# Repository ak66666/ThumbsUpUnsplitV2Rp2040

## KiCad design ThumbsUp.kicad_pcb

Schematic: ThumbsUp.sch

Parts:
BOOTSEL1: TL1016AAF220QG; Manufacturer_Part_Number TL1016AAF220QG; Mouser Part Number 612-TL1016AAF220QG
C1, C2, C6, C7, C10, C13, C14, C15, C16, C17: 0.1uF; C_0805_2012Metric
C3, C12: 1uF; C_0805_2012Metric
C4, C5: 27pF; C_0805_2012Metric
C9, C11: 10uF; C_0805_2012Metric
D1, D2, D3, D4, D5, D6, D7, D8, D9, D10, D11, D12, D13, D14, D15, D16, D17, D18, D19, D20, D21, D22, D23, D24, D25, D26, D27, D28, D29, D30, D31, D32, D33, D34, D35, D36, D37, D38, D39, D40, D41, D42, D43, D44: D_Small; D_SOD-123
F1: Polyfuse; Fuse_1206_3216Metric
H1, H2, H3: MountingHole_Pad; MountingHole_6.4mm_M6_Pad_Via
IC1: RP2040; QFN40P700X700X90-57N-D; Manufacturer_Part_Number RP2040
IC2: W25Q128JVSIM; SOIC127P790X216-8N; Manufacturer_Part_Number W25Q128JVSIM; Mouser Part Number 454-W25Q128JVSIM
J1, J2, J4, J6, J7, J8, J24, J25, J26, J27: Conn_01x04_Male; PinHeader_1x04_P2.54mm_Vertical
J3, J5, J20, J21, J22, J23, J28, J29, J30, J31: Conn_01x04_Female; PinSocket_1x04_P2.54mm_Vertical
J9, J11, J13, J15, J17: Raiser_Female; PinSocket_1x04_P2.54mm_Vertical
J10, J12, J14, J16, J18: Raiser_Male; PinHeader_1x04_P2.54mm_Vertical
J19: 52559-1233; 525591233; Mouser Part Number 538-52559-1233
J32: USB_C_Receptacle_USB2.0; USB_C_Receptacle_Palconn_UTC16-G
J33: STX-3501-3N; STX35013N; Manufacturer_Part_Number STX-3501-3N; Mouser Part Number 806-STX-3501-3N
MX1: SwESC; Kailh_socket_PG1350_optional
MX2: SwTAB; Kailh_socket_PG1350_optional
MX3: SwLCTL; Kailh_socket_PG1350_optional
MX4: SwQ; Kailh_socket_PG1350_optional
MX5: SwA; Kailh_socket_PG1350_optional
MX6: SwZ; Kailh_socket_PG1350_optional
MX7: SwW; Kailh_socket_PG1350_optional
MX8: SwS; Kailh_socket_PG1350_optional
MX9: SwX; Kailh_socket_PG1350_optional
MX10: SwLWIN; Kailh_socket_PG1350_optional
MX11: SwE; Kailh_socket_PG1350_optional
MX12: SwD; Kailh_socket_PG1350_optional
MX13: SwC; Kailh_socket_PG1350_optional
MX14: SwLALT; Kailh_socket_PG1350_optional
MX15: SwR; Kailh_socket_PG1350_optional
MX16: SwF; Kailh_socket_PG1350_optional
MX17: SwV; Kailh_socket_PG1350_optional
MX18: SwLMOD; Kailh_socket_PG1350_optional
MX19: SwT; Kailh_socket_PG1350_optional
MX20: SwG; Kailh_socket_PG1350_optional
MX21: SwB; Kailh_socket_PG1350_optional
MX22: SwLSHFT; Kailh_socket_PG1350_optional
MX23: SwY; Kailh_socket_PG1350_optional
MX24: SwH; Kailh_socket_PG1350_optional
MX25: SwN; Kailh_socket_PG1350_optional
MX26: SwRSHFT; Kailh_socket_PG1350_optional
MX27: SwU; Kailh_socket_PG1350_optional
MX28: SwJ; Kailh_socket_PG1350_optional
MX29: SwM; Kailh_socket_PG1350_optional
MX30: SwRMOD; Kailh_socket_PG1350_optional
MX31: SwI; Kailh_socket_PG1350_optional
MX32: SwK; Kailh_socket_PG1350_optional
MX33: SwCOMMA; Kailh_socket_PG1350_optional
MX34: SwRALT; Kailh_socket_PG1350_optional
MX35: SwO; Kailh_socket_PG1350_optional
MX36: SwL; Kailh_socket_PG1350_optional
MX37: SwDOT; Kailh_socket_PG1350_optional
MX38: SwMENU; Kailh_socket_PG1350_optional
MX39: SwP; Kailh_socket_PG1350_optional
MX40: SwCOLON; Kailh_socket_PG1350_optional
MX41: Sw?; Kailh_socket_PG1350_optional
MX42: SwBKSP; Kailh_socket_PG1350_optional
MX43: SwENTER; Kailh_socket_PG1350_optional
MX44: SwRCTRL; Kailh_socket_PG1350_optional
R1, R2: 27.4; R_0805_2012Metric
R3: 10k; R_0805_2012Metric
R4, R5: 4.7k; R_0805_2012Metric
R6: 1k; R_0805_2012Metric
R7: DNF; R_0805_2012Metric
R8, R9: 5.1k; R_0805_2012Metric
RUN1: TL1016AAF220QG; Manufacturer_Part_Number TL1016AAF220QG; Mouser Part Number 612-TL1016AAF220QG
U1: NCP1117-3.3_SOT223; SOT-223-3_TabPin2
Y1: ABLS-12.000MHZ-B4-T; HC%2f49US-(AT49)_1

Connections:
+1V1: C12.1, C13.1, C14.1, IC1.23 (DVDD_1), IC1.45 (VREG_VOUT), IC1.50 (DVDD_2)
+3V3: C1.1, C2.1, C3.1, C6.1, C7.1, C10.1, C11.1, C15.1, C16.1, C17.1, IC1.1 (IOVDD_1), IC1.10 (IOVDD_2), IC1.22 (IOVDD_3), IC1.33 (IOVDD_4), IC1.42 (IOVDD_5), IC1.43 (ADC_AVDD), IC1.44 (VREG_VIN), IC1.48 (USB_VDD), IC1.49 (IOVDD_6), IC2.8 (VCC), J18.1, R4.1, R5.2, R7.2, U1.2 (VO)
+5V: C9.1, F1.1, U1.3 (VI)
COL0: IC1.35 (GPIO23), J20.4
COL1: IC1.36 (GPIO24), J20.3
COL2: IC1.37 (GPIO25), J20.2, MX10.1 (COL)
COL3: IC1.38 (GPIO26/ADC0), J20.1, MX14.1 (COL)
COL4: IC1.34 (GPIO22), J4.1, MX15.1 (COL), MX16.1 (COL), MX17.1 (COL)
COL5: IC1.39 (GPIO27/ADC1), J4.4, MX19.1 (COL), MX20.1 (COL), MX21.1 (COL)
COL6: IC1.5 (GPIO3), J6.1, MX23.1 (COL), MX24.1 (COL), MX25.1 (COL)
COL7: IC1.4 (GPIO2), J6.4, MX27.1 (COL), MX28.1 (COL), MX29.1 (COL)
COL8: IC1.6 (GPIO4), J24.1, MX34.1 (COL)
COL9: IC1.7 (GPIO5), J24.2, MX38.1 (COL)
COLA: IC1.8 (GPIO6), J24.3
COLB: IC1.9 (GPIO7), J24.4
D+: J32.A6 (D+), J32.B6 (D+), R2.2
D-: J32.A7 (D-), J32.B7 (D-), R1.2
GND: BOOTSEL1.3, BOOTSEL1.4, C1.2, C2.2, C3.2, C4.2, C5.2, C6.2, C7.2, C9.2, C10.2, C11.2, C12.2, C13.2, C14.2, C15.2, C16.2, C17.2, IC1.19 (TESTEN), IC1.57 (GND), IC2.4 (GND), J11.1, J11.2, J11.3, J11.4, J15.1, J15.2, J15.3, J15.4, J18.4, J32.A1 (GND), J32.A12 (GND), J32.B1 (GND), J32.B12 (GND), J32.S1 (SHIELD), R8.2, R9.1, RUN1.3, RUN1.4, U1.1 (GND)
GND-TOP: J17.4, J19.11
unnamed: BOOTSEL1.1, BOOTSEL1.2, R3.1
unnamed: C5.1, R6.2, Y1.1
unnamed: D1.2 (A), J21.4
unnamed: D2.2 (A), J21.3
unnamed: D3.2 (A), J21.2
unnamed: D4.2 (A), J21.1
unnamed: D5.2 (A), J22.4
unnamed: D6.2 (A), J22.3
unnamed: D7.2 (A), J22.2
unnamed: D8.2 (A), J22.1
unnamed: D9.2 (A), J23.4
unnamed: D10.2 (A), J23.3
unnamed: D11.2 (A), J23.2
unnamed: D12.2 (A), J23.1
unnamed: D13.2 (A), MX14.2 (ROW)
unnamed: D14.2 (A), MX10.2 (ROW)
unnamed: D15.2 (A), MX15.2 (ROW)
unnamed: D16.2 (A), MX16.2 (ROW)
unnamed: D17.2 (A), MX17.2 (ROW)
unnamed: D18.2 (A), J4.2
unnamed: D19.2 (A), J4.3
unnamed: D20.2 (A), MX19.2 (ROW)
unnamed: D21.2 (A), MX20.2 (ROW)
unnamed: D22.2 (A), MX21.2 (ROW)
unnamed: D23.2 (A), MX23.2 (ROW)
unnamed: D24.2 (A), MX24.2 (ROW)
unnamed: D25.2 (A), MX25.2 (ROW)
unnamed: D26.2 (A), MX27.2 (ROW)
unnamed: D27.2 (A), MX28.2 (ROW)
unnamed: D28.2 (A), MX29.2 (ROW)
unnamed: D29.2 (A), J6.2
unnamed: D30.2 (A), J6.3
unnamed: D31.2 (A), J25.4
unnamed: D32.2 (A), J25.3
unnamed: D33.2 (A), J25.2
unnamed: D34.2 (A), J25.1
unnamed: D35.2 (A), J26.4
unnamed: D36.2 (A), J26.3
unnamed: D37.2 (A), J26.2
unnamed: D38.2 (A), J26.1
unnamed: D39.2 (A), J27.4
unnamed: D40.2 (A), J27.3
unnamed: D41.2 (A), J27.2
unnamed: D42.2 (A), J27.1
unnamed: D43.2 (A), MX34.2 (ROW)
unnamed: D44.2 (A), MX38.2 (ROW)
unnamed: F1.2, J32.A4 (VBUS), J32.A9 (VBUS), J32.B4 (VBUS), J32.B9 (VBUS)
unnamed: H1.1, H2.1, H3.1, J12.1, J12.2, J12.3, J12.4, J16.1, J16.2, J16.3, J16.4
unnamed: IC1.26 (RUN), RUN1.1, RUN1.2
unnamed: IC1.46 (USB_DM), R1.1
unnamed: IC1.47 (USB_DP), R2.1
unnamed: J1.1, MX11.1 (COL), MX12.1 (COL), MX13.1 (COL)
unnamed: J1.2, MX7.1 (COL), MX8.1 (COL), MX9.1 (COL)
unnamed: J1.3, MX4.1 (COL), MX5.1 (COL), MX6.1 (COL)
unnamed: J1.4, MX1.1 (COL), MX2.1 (COL), MX3.1 (COL)
unnamed: J2.1, MX1.2 (ROW)
unnamed: J2.2, MX4.2 (ROW)
unnamed: J2.3, MX7.2 (ROW)
unnamed: J2.4, MX11.2 (ROW)
unnamed: J3.1, MX22.1 (COL)
unnamed: J3.2, MX22.2 (ROW)
unnamed: J3.3, MX18.1 (COL)
unnamed: J3.4, MX18.2 (ROW)
unnamed: J5.1, MX30.1 (COL)
unnamed: J5.2, MX30.2 (ROW)
unnamed: J5.3, MX26.1 (COL)
unnamed: J5.4, MX26.2 (ROW)
unnamed: J7.1, MX2.2 (ROW)
unnamed: J7.2, MX5.2 (ROW)
unnamed: J7.3, MX8.2 (ROW)
unnamed: J7.4, MX12.2 (ROW)
unnamed: J8.1, MX3.2 (ROW)
unnamed: J8.2, MX6.2 (ROW)
unnamed: J8.3, MX9.2 (ROW)
unnamed: J8.4, MX13.2 (ROW)
unnamed: J28.1, MX31.1 (COL), MX32.1 (COL), MX33.1 (COL)
unnamed: J28.2, MX35.1 (COL), MX36.1 (COL), MX37.1 (COL)
unnamed: J28.3, MX39.1 (COL), MX40.1 (COL), MX41.1 (COL)
unnamed: J28.4, MX42.1 (COL), MX43.1 (COL), MX44.1 (COL)
unnamed: J29.1, MX42.2 (ROW)
unnamed: J29.2, MX39.2 (ROW)
unnamed: J29.3, MX35.2 (ROW)
unnamed: J29.4, MX31.2 (ROW)
unnamed: J30.1, MX43.2 (ROW)
unnamed: J30.2, MX40.2 (ROW)
unnamed: J30.3, MX36.2 (ROW)
unnamed: J30.4, MX32.2 (ROW)
unnamed: J31.1, MX44.2 (ROW)
unnamed: J31.2, MX41.2 (ROW)
unnamed: J31.3, MX37.2 (ROW)
unnamed: J31.4, MX33.2 (ROW)
unnamed: J32.A5 (CC1), R8.1
unnamed: J32.B5 (CC2), R9.2
QSPI_SCLK: IC1.52 (QSPI_SCLK), IC2.6 (CLK)
QSPI_SD0: IC1.53 (QSPI_SD0), IC2.5 (DI_(IO0))
QSPI_SD1: IC1.55 (QSPI_SD1), IC2.2 (DO_(IO1))
QSPI_SD2: IC1.54 (QSPI_SD2), IC2.3 (~WP_(IO2))
QSPI_SD3: IC1.51 (QSPI_SD3), IC2.7 (~HOLD_OR_~/RESET_(IO3))
QSPI_SSN: IC1.56 (QSPI_SS_N), IC2.1 (~CS), R3.2, R7.1
ROW0: D1.1 (K), D2.1 (K), D3.1 (K), D4.1 (K), D15.1 (K), D20.1 (K), D23.1 (K), D26.1 (K), D31.1 (K), D32.1 (K), D33.1 (K), D34.1 (K), IC1.2 (GPIO0)
ROW1: D5.1 (K), D6.1 (K), D7.1 (K), D8.1 (K), D16.1 (K), D21.1 (K), D24.1 (K), D27.1 (K), D35.1 (K), D36.1 (K), D37.1 (K), D38.1 (K), IC1.3 (GPIO1)
ROW2: D9.1 (K), D10.1 (K), D11.1 (K), D12.1 (K), D17.1 (K), D22.1 (K), D25.1 (K), D28.1 (K), D39.1 (K), D40.1 (K), D41.1 (K), D42.1 (K), IC1.41 (GPIO29/ADC3)
ROW3: D13.1 (K), D14.1 (K), D18.1 (K), D19.1 (K), D29.1 (K), D30.1 (K), D43.1 (K), D44.1 (K), IC1.40 (GPIO28/ADC2)
SCL: IC1.30 (GPIO19), J18.3, R4.2
SCL-TOP: J17.3, J19.9
SDA: IC1.29 (GPIO18), J18.2, R5.1
SDA-TOP: J17.2, J19.10
VCC-TOP: J17.1, J19.12
XIN: C4.1, IC1.20 (XIN), Y1.2
XOUT: IC1.21 (XOUT), R6.1

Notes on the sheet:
As in Planck/rev4: #define MATRIX_ROW_PINS { D3, D5, B5, B6 } #define MATRIX_COL_PINS { F1, F0, B0, C7, F4, F5, F6, F7, D4, D6, B4, D7 } #define DIODE_DIRECTION COL2ROW
Pull-up for Cirque Trackpad

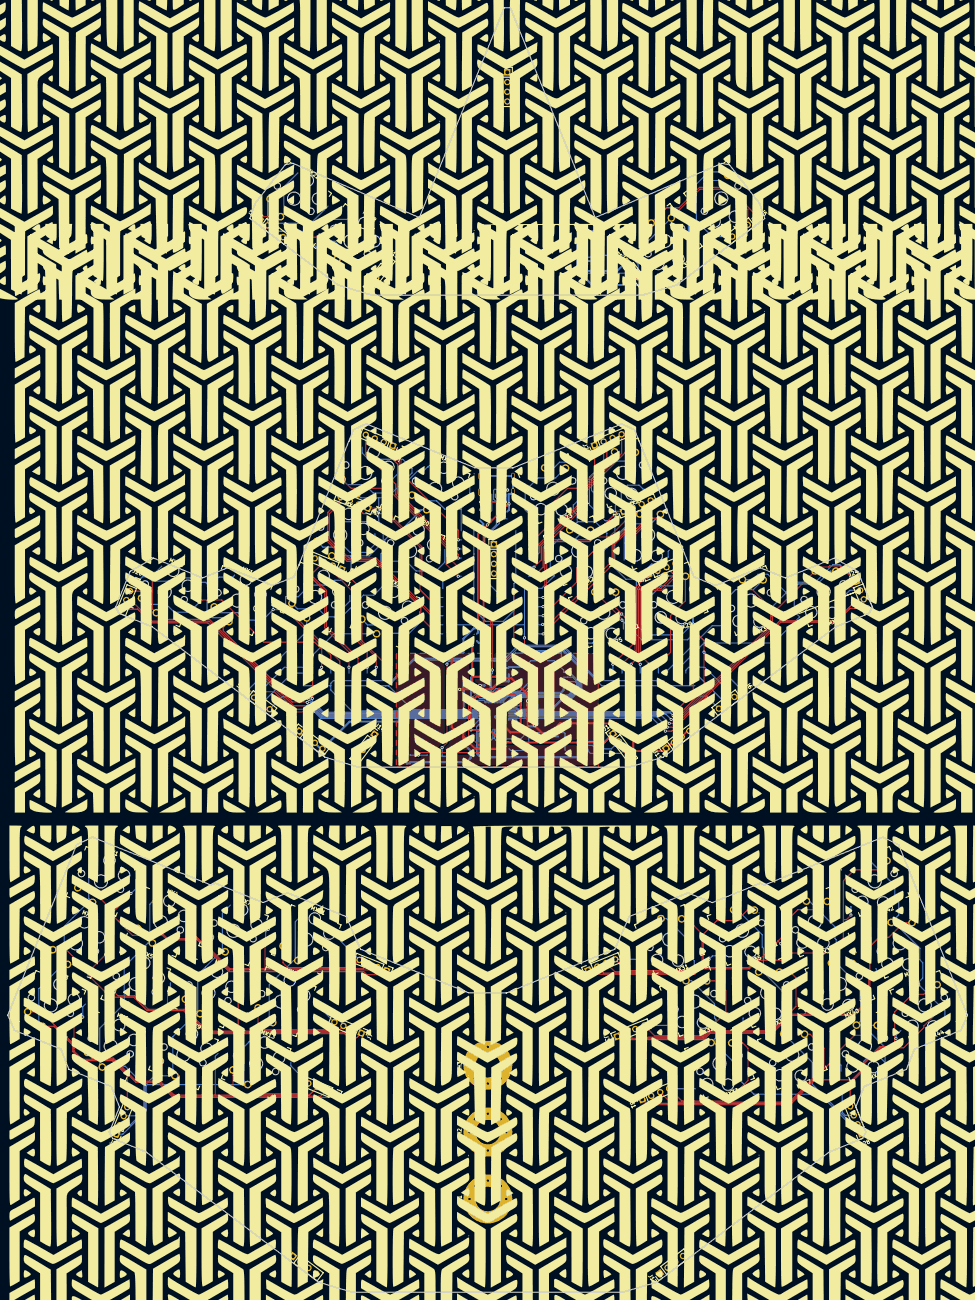
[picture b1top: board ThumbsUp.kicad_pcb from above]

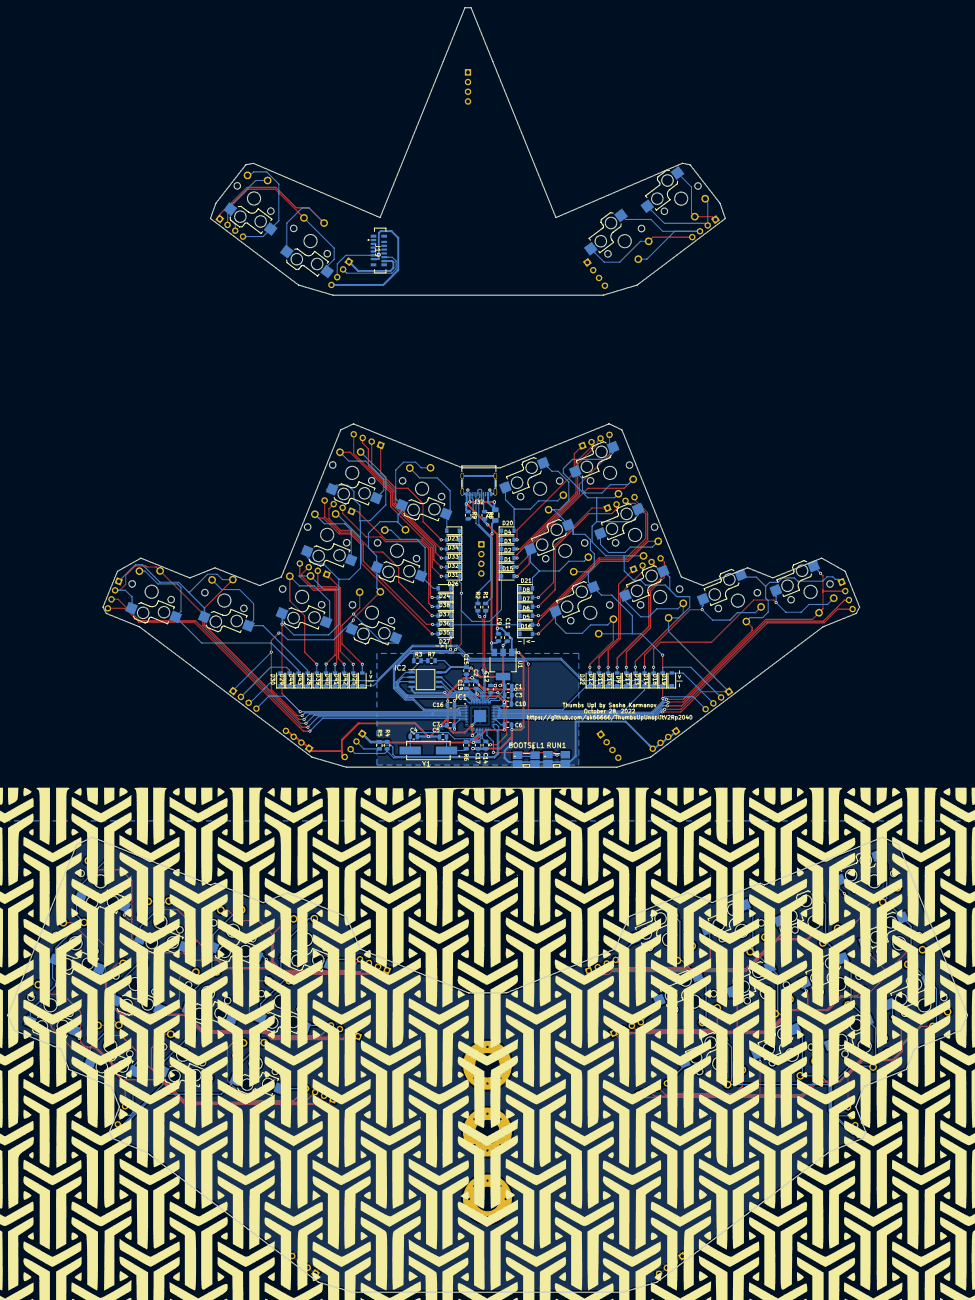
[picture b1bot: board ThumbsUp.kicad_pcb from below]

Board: 2 copper layers, 251.1 x 336.1 mm, 155 parts (78 on the bottom side), 129 nets.

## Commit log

2022-12-11 Wiring started
2022-12-11 Wiring continued
2022-12-12 Prepared Gerbers
2022-12-17 Replaced the mini-USB connector with USB-C
2022-12-24 Some schema elements rearranged
2022-12-25 Restored the schematics file which was overridden by mistake
2023-01-01 Added a missing line SS-N
2023-03-14 Reviewing USB-C Option before ordering
2023-03-31 Retraced the lower PCB
2023-05-16 Modified schematics: added third thumb button, replaced pushbuttons with through-hole ones
